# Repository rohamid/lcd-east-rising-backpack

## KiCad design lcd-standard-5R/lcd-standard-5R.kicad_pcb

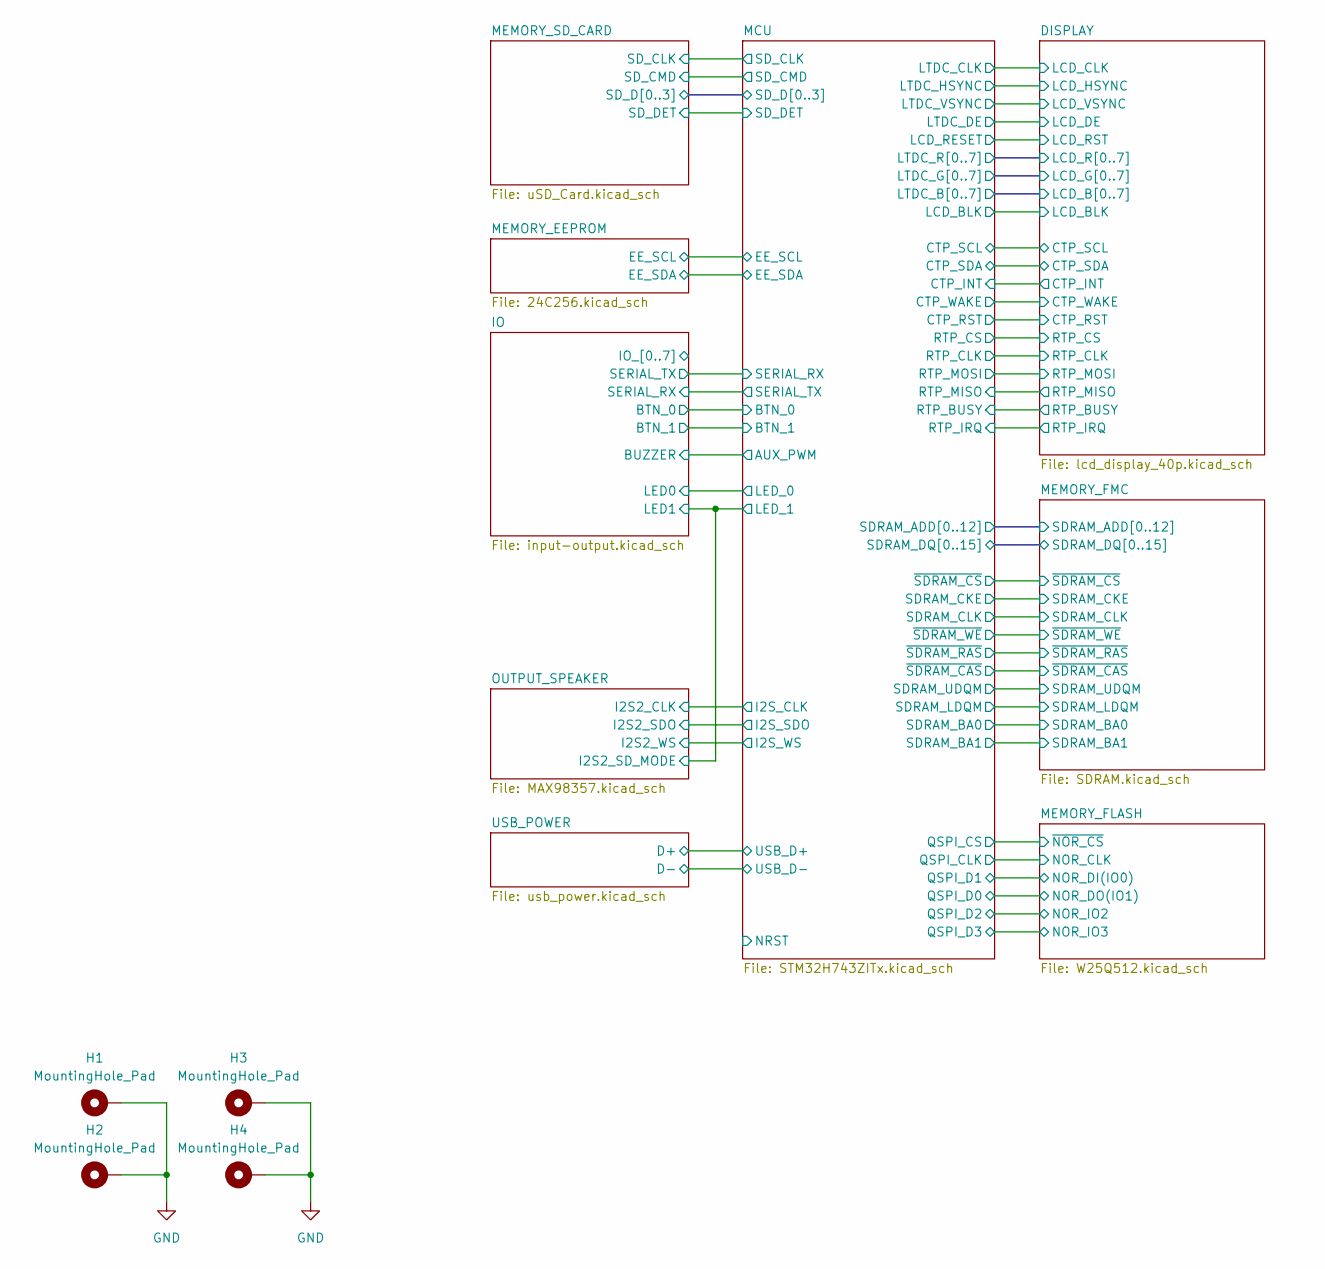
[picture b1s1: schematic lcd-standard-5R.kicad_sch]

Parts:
H1, H2, H3, H4: MountingHole_Pad; MountingHole_3.2mm_M3_Pad_Via

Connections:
GND: H1.1, H2.1, H3.1, H4.1; also elsewhere on the board

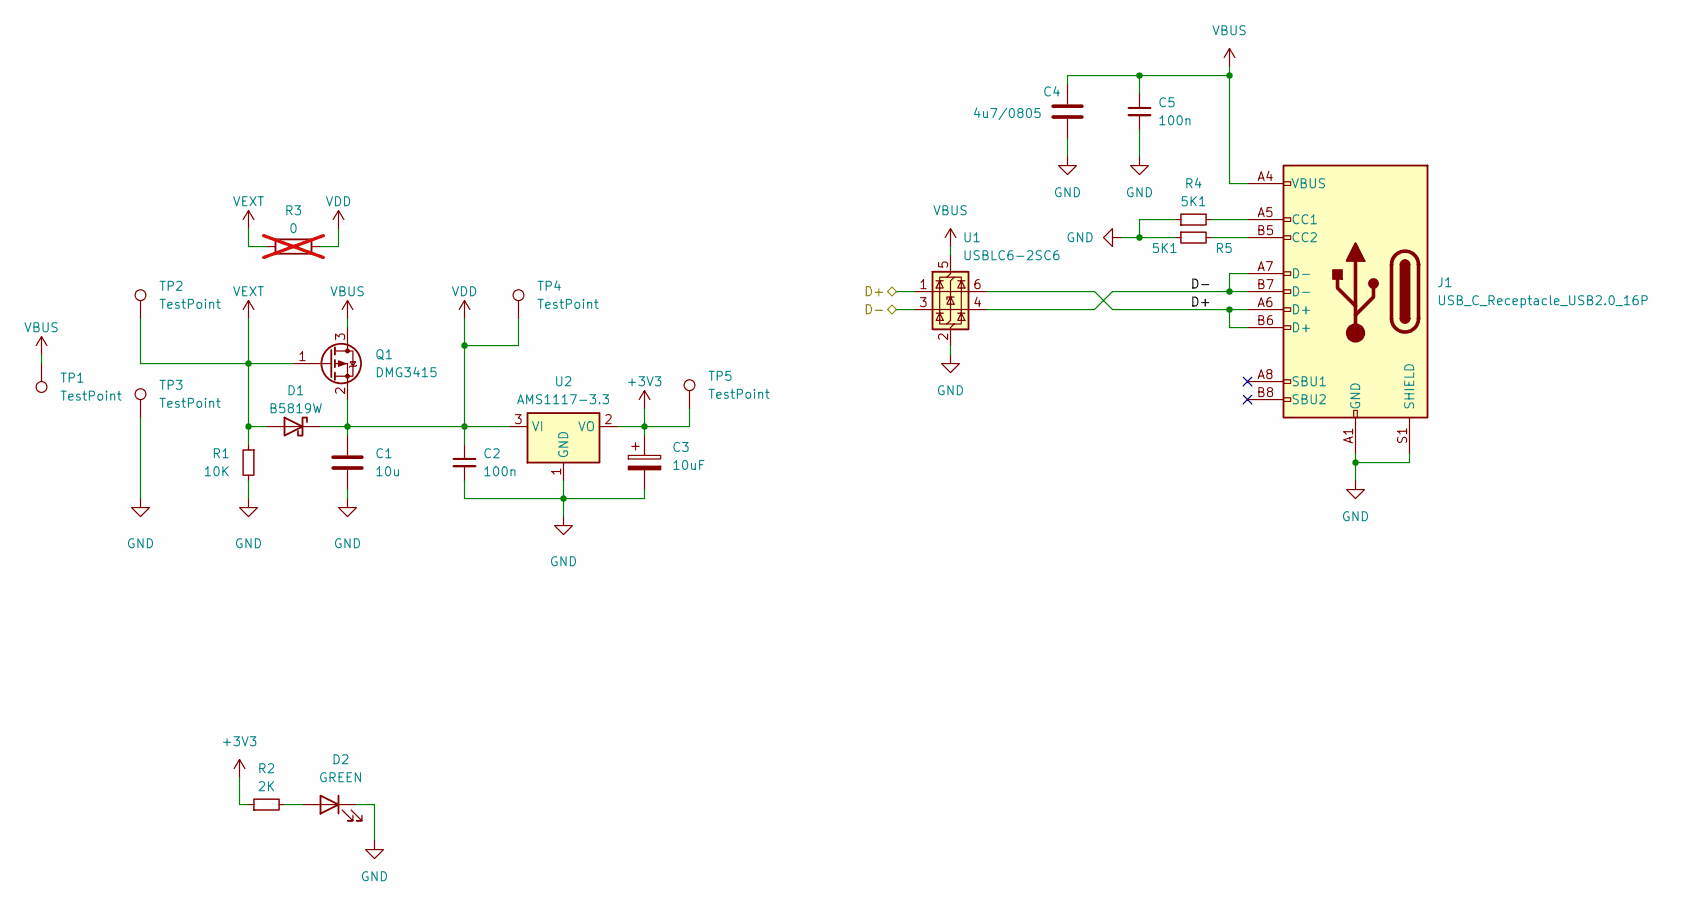
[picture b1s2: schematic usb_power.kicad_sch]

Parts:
C1: 10u; C_0805_2012Metric; JLCPCB Part # C15850
C2, C5: 100n; C_0402_1005Metric; JLCPCB Part # C307331
C3: 10uF; CP_EIA-3216-18_Kemet-A; JLCPCB Part # C7171
C4: 4u7/0805; C_0805_2012Metric; JLCPCB Part # C1779
D1: B5819W; D_SOD-123; JLCPCB Part # C7420330
D2: GREEN; LED_0805_2012Metric; JLCPCB Part # C2297
J1: USB_C_Receptacle_USB2.0_16P; USB_C_Receptacle_G-Switch_GT-USB-7010ASV; JLCPCB Part # C963412
Q1: DMG3415; SOT-23; JLCPCB Part # C7202986
R1: 10K; R_0402_1005Metric; JLCPCB Part # C25744
R2: 2K; R_0402_1005Metric; JLCPCB Part # C4109
R3: 0; R_1206_3216Metric; not fitted
R4, R5: 5K1; R_0402_1005Metric; JLCPCB Part # C25905
TP1, TP2, TP3, TP4, TP5: TestPoint; TestPoint_Pad_D1.0mm
U1: USBLC6-2SC6; SOT-23-6; JLCPCB Part # C2827654
U2: AMS1117-3.3; SOT-223-3_TabPin2; JLCPCB Part # C6186

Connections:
+3V3: C3.1, R2.1, TP5.1, U2.2 (VO); also elsewhere on the board
/USB_POWER/D+: J1.A6 (D+), J1.B6 (D+), U1.1 (I/O1), U1.6 (I/O1); also elsewhere on the board
/USB_POWER/D-: J1.A7 (D-), J1.B7 (D-), U1.3 (I/O2), U1.4 (I/O2); also elsewhere on the board
GND: C1.2, C2.2, C3.2, C4.2, C5.2, D2.1 (K), J1.A1 (GND), J1.A12 (GND), J1.B1 (GND), J1.B12 (GND), J1.S1 (SHIELD), R1.2, R4.1, R5.1, TP3.1, U1.2 (GND), U2.1 (GND); also elsewhere on the board
unnamed: D2.2 (A), R2.2
unnamed: J1.A5 (CC1), R4.2
unnamed: J1.B5 (CC2), R5.2
VBUS: C4.1, C5.1, J1.A4 (VBUS), J1.A9 (VBUS), J1.B4 (VBUS), J1.B9 (VBUS), Q1.3 (D), TP1.1, U1.5 (VBUS)
VDD: C1.1, C2.1, D1.1 (K), Q1.2 (S), R3.2, TP4.1, U2.3 (VI); also elsewhere on the board
VEXT: D1.2 (A), Q1.1 (G), R1.1, R3.1, TP2.1; also elsewhere on the board

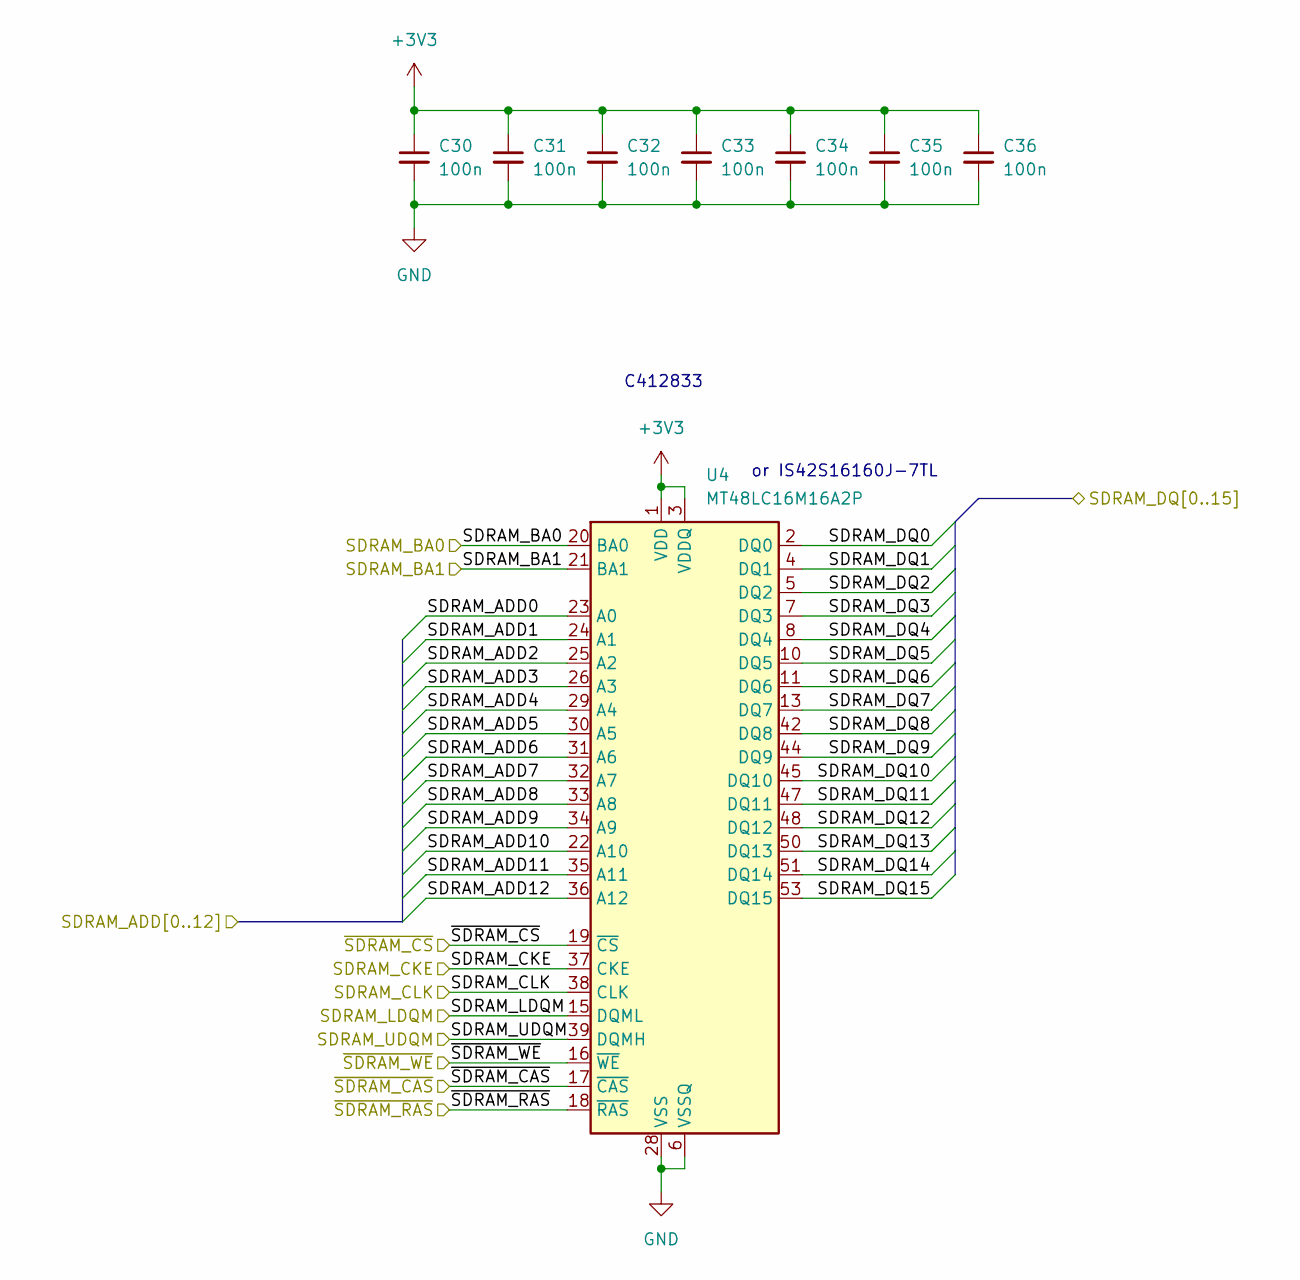
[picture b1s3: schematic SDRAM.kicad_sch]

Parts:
C30, C31, C32, C33, C34, C35, C36: 100n; C_0402_1005Metric; JLCPCB Part # C307331
U4: MT48LC16M16A2P; TSOP-II-54_22.2x10.16mm_P0.8mm; JLCPCB Part # C412833

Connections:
+3V3: C30.1, C31.1, C32.1, C33.1, C34.1, C35.1, C36.1, U4.1 (VDD), U4.3 (VDDQ), U4.9 (VDDQ), U4.14 (VDD), U4.27 (VDD), U4.43 (VDDQ), U4.49 (VDDQ); also elsewhere on the board
/MCU/SDRAM_ADD0: U4.23 (A0); also elsewhere on the board
/MCU/SDRAM_ADD1: U4.24 (A1); also elsewhere on the board
/MCU/SDRAM_ADD2: U4.25 (A2); also elsewhere on the board
/MCU/SDRAM_ADD3: U4.26 (A3); also elsewhere on the board
/MCU/SDRAM_ADD4: U4.29 (A4); also elsewhere on the board
/MCU/SDRAM_ADD5: U4.30 (A5); also elsewhere on the board
/MCU/SDRAM_ADD6: U4.31 (A6); also elsewhere on the board
/MCU/SDRAM_ADD7: U4.32 (A7); also elsewhere on the board
/MCU/SDRAM_ADD8: U4.33 (A8); also elsewhere on the board
/MCU/SDRAM_ADD9: U4.34 (A9); also elsewhere on the board
/MCU/SDRAM_ADD10: U4.22 (A10); also elsewhere on the board
/MCU/SDRAM_ADD11: U4.35 (A11); also elsewhere on the board
/MCU/SDRAM_ADD12: U4.36 (A12); also elsewhere on the board
/MCU/SDRAM_DQ0: U4.2 (DQ0); also elsewhere on the board
/MCU/SDRAM_DQ1: U4.4 (DQ1); also elsewhere on the board
/MCU/SDRAM_DQ2: U4.5 (DQ2); also elsewhere on the board
/MCU/SDRAM_DQ3: U4.7 (DQ3); also elsewhere on the board
/MCU/SDRAM_DQ4: U4.8 (DQ4); also elsewhere on the board
/MCU/SDRAM_DQ5: U4.10 (DQ5); also elsewhere on the board
/MCU/SDRAM_DQ6: U4.11 (DQ6); also elsewhere on the board
/MCU/SDRAM_DQ7: U4.13 (DQ7); also elsewhere on the board
/MCU/SDRAM_DQ8: U4.42 (DQ8); also elsewhere on the board
/MCU/SDRAM_DQ9: U4.44 (DQ9); also elsewhere on the board
/MCU/SDRAM_DQ10: U4.45 (DQ10); also elsewhere on the board
/MCU/SDRAM_DQ11: U4.47 (DQ11); also elsewhere on the board
/MCU/SDRAM_DQ12: U4.48 (DQ12); also elsewhere on the board
/MCU/SDRAM_DQ13: U4.50 (DQ13); also elsewhere on the board
/MCU/SDRAM_DQ14: U4.51 (DQ14); also elsewhere on the board
/MCU/SDRAM_DQ15: U4.53 (DQ15); also elsewhere on the board
/MEMORY_FMC/SDRAM_BA0: U4.20 (BA0); also elsewhere on the board
/MEMORY_FMC/SDRAM_BA1: U4.21 (BA1); also elsewhere on the board
/MEMORY_FMC/SDRAM_CKE: U4.37 (CKE); also elsewhere on the board
/MEMORY_FMC/SDRAM_CLK: U4.38 (CLK); also elsewhere on the board
/MEMORY_FMC/SDRAM_LDQM: U4.15 (DQML); also elsewhere on the board
/MEMORY_FMC/SDRAM_UDQM: U4.39 (DQMH); also elsewhere on the board
/MEMORY_FMC/~SDRAM_CAS: U4.17 (~CAS); also elsewhere on the board
/MEMORY_FMC/~SDRAM_CS: U4.19 (~CS); also elsewhere on the board
/MEMORY_FMC/~SDRAM_RAS: U4.18 (~RAS); also elsewhere on the board
/MEMORY_FMC/~SDRAM_WE: U4.16 (~WE); also elsewhere on the board
GND: C30.2, C31.2, C32.2, C33.2, C34.2, C35.2, C36.2, U4.6 (VSSQ), U4.12 (VSSQ), U4.28 (VSS), U4.41 (VSS), U4.46 (VSSQ), U4.52 (VSSQ), U4.54 (VSS); also elsewhere on the board

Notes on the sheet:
C412833
or IS42S16160J-7TL

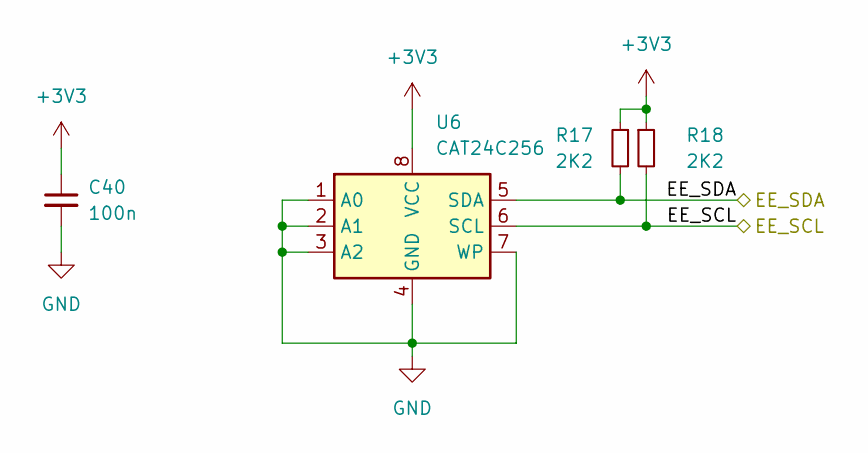
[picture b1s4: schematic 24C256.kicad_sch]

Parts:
C40: 100n; C_0402_1005Metric; JLCPCB Part # C307331
R17, R18: 2K2; R_0402_1005Metric; JLCPCB Part # C25879
U6: CAT24C256; SOIC-8_3.9x4.9mm_P1.27mm; JLCPCB Part # C6482

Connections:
+3V3: C40.1, R17.1, R18.1, U6.8 (VCC); also elsewhere on the board
/MEMORY_EEPROM/EE_SCL: R18.2, U6.6 (SCL); also elsewhere on the board
/MEMORY_EEPROM/EE_SDA: R17.2, U6.5 (SDA); also elsewhere on the board
GND: C40.2, U6.1 (A0), U6.2 (A1), U6.3 (A2), U6.4 (GND), U6.7 (WP); also elsewhere on the board

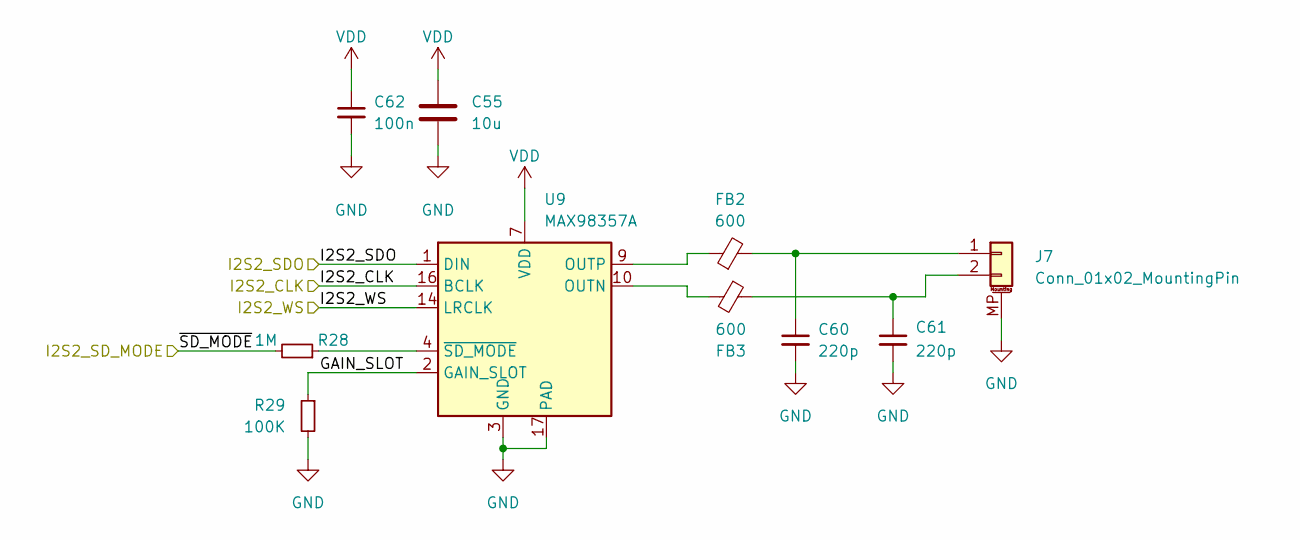
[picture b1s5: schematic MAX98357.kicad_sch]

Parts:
C55: 10u; C_0805_2012Metric; JLCPCB Part # C15850
C60, C61: 220p; C_0805_2012Metric; JLCPCB Part # C107145
C62: 100n; C_0402_1005Metric; JLCPCB Part # C307331
FB2, FB3: 600; L_0805_2012Metric; JLCPCB Part # C1017
J7: Conn_01x02_MountingPin; Hirose_DF13C_CL535-0402-2-51_1x02-1MP_P1.25mm_Vertical; JLCPCB Part # C7419891
R28: 1M; R_0402_1005Metric; JLCPCB Part # C26083
R29: 100K; R_0402_1005Metric; JLCPCB Part # C25741
U9: MAX98357A; TQFN-16-1EP_3x3mm_P0.5mm_EP1.23x1.23mm; JLCPCB Part # C910544

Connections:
/OUTPUT_SPEAKER/GAIN_SLOT: R29.1, U9.2 (GAIN_SLOT)
/OUTPUT_SPEAKER/I2S2_CLK: U9.16 (BCLK); also elsewhere on the board
/OUTPUT_SPEAKER/I2S2_SDO: U9.1 (DIN); also elsewhere on the board
/OUTPUT_SPEAKER/I2S2_WS: U9.14 (LRCLK); also elsewhere on the board
/OUTPUT_SPEAKER/~SD_MODE: R28.2; also elsewhere on the board
GND: C55.2, C60.2, C61.2, C62.2, J7.MP (MountPin), R29.2, U9.3 (GND), U9.11 (GND), U9.15 (GND), U9.17 (PAD); also elsewhere on the board
unnamed: C60.1, FB2.2, J7.1
unnamed: C61.1, FB3.1, J7.2
unnamed: FB3.2, U9.10 (OUTN)
unnamed: FB2.1, U9.9 (OUTP)
unnamed: R28.1, U9.4 (~SD_MODE)
VDD: C55.1, C62.1, U9.7 (VDD), U9.8 (VDD); also elsewhere on the board

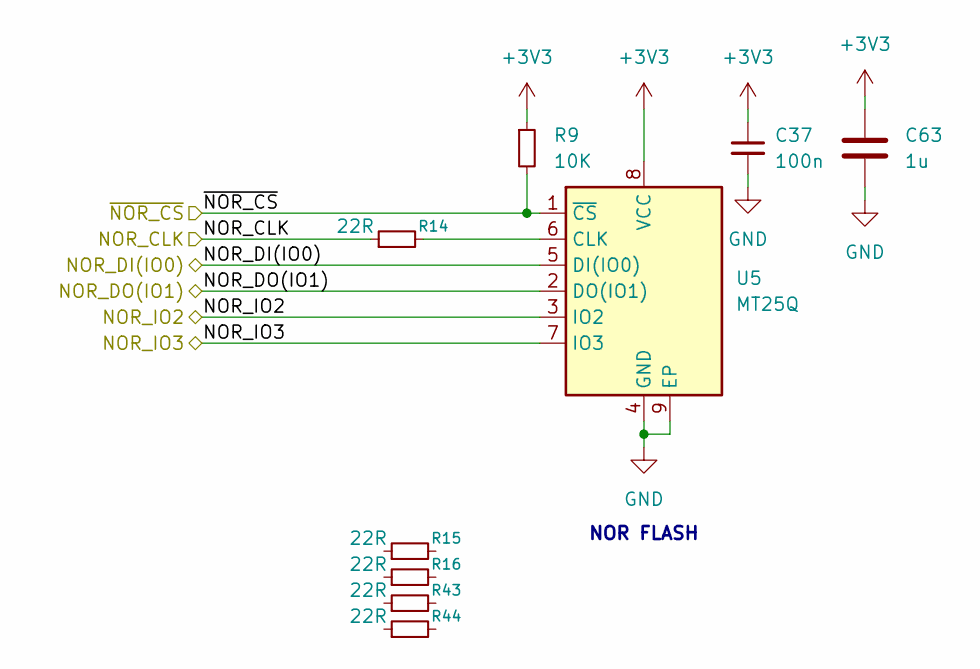
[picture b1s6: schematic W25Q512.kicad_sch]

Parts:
C37: 100n; C_0402_1005Metric; JLCPCB Part # C307331
C63: 1u; C_0603_1608Metric; JLCPCB Part # C15849
R9: 10K; R_0402_1005Metric; JLCPCB Part # C25744
R14, R15, R16, R43, R44: 22R; R_0201_0603Metric
U5: MT25Q; SON127P800X600X80-9N; JLCPCB Part # C2061007

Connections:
+3V3: C37.1, C63.1, R9.1, U5.8 (VCC); also elsewhere on the board
/MEMORY_FLASH/NOR_CLK: R14.1; also elsewhere on the board
/MEMORY_FLASH/NOR_DI(IO0): U5.5 (DI(IO0)); also elsewhere on the board
/MEMORY_FLASH/NOR_DO(IO1): U5.2 (DO(IO1)); also elsewhere on the board
/MEMORY_FLASH/NOR_IO2: U5.3 (IO2); also elsewhere on the board
/MEMORY_FLASH/NOR_IO3: U5.7 (IO3); also elsewhere on the board
/MEMORY_FLASH/~NOR_CS: R9.2, U5.1 (~CS); also elsewhere on the board
GND: C37.2, C63.2, U5.4 (GND), U5.9 (EP); also elsewhere on the board
unnamed: R14.2, U5.6 (CLK)

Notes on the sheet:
NOR FLASH

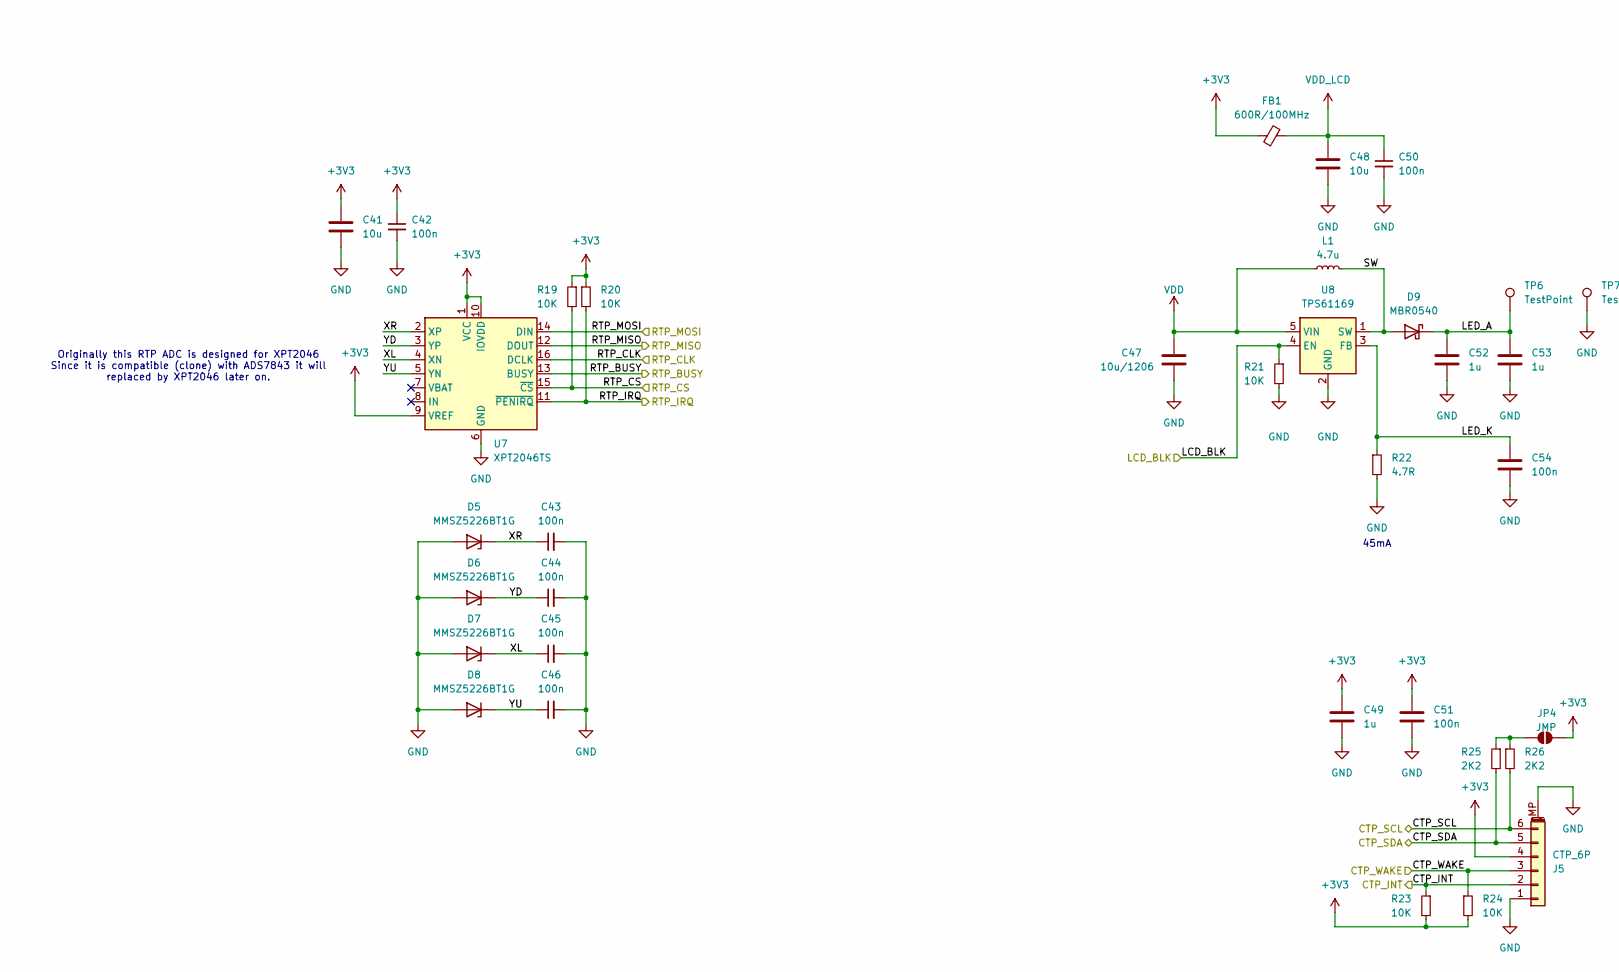
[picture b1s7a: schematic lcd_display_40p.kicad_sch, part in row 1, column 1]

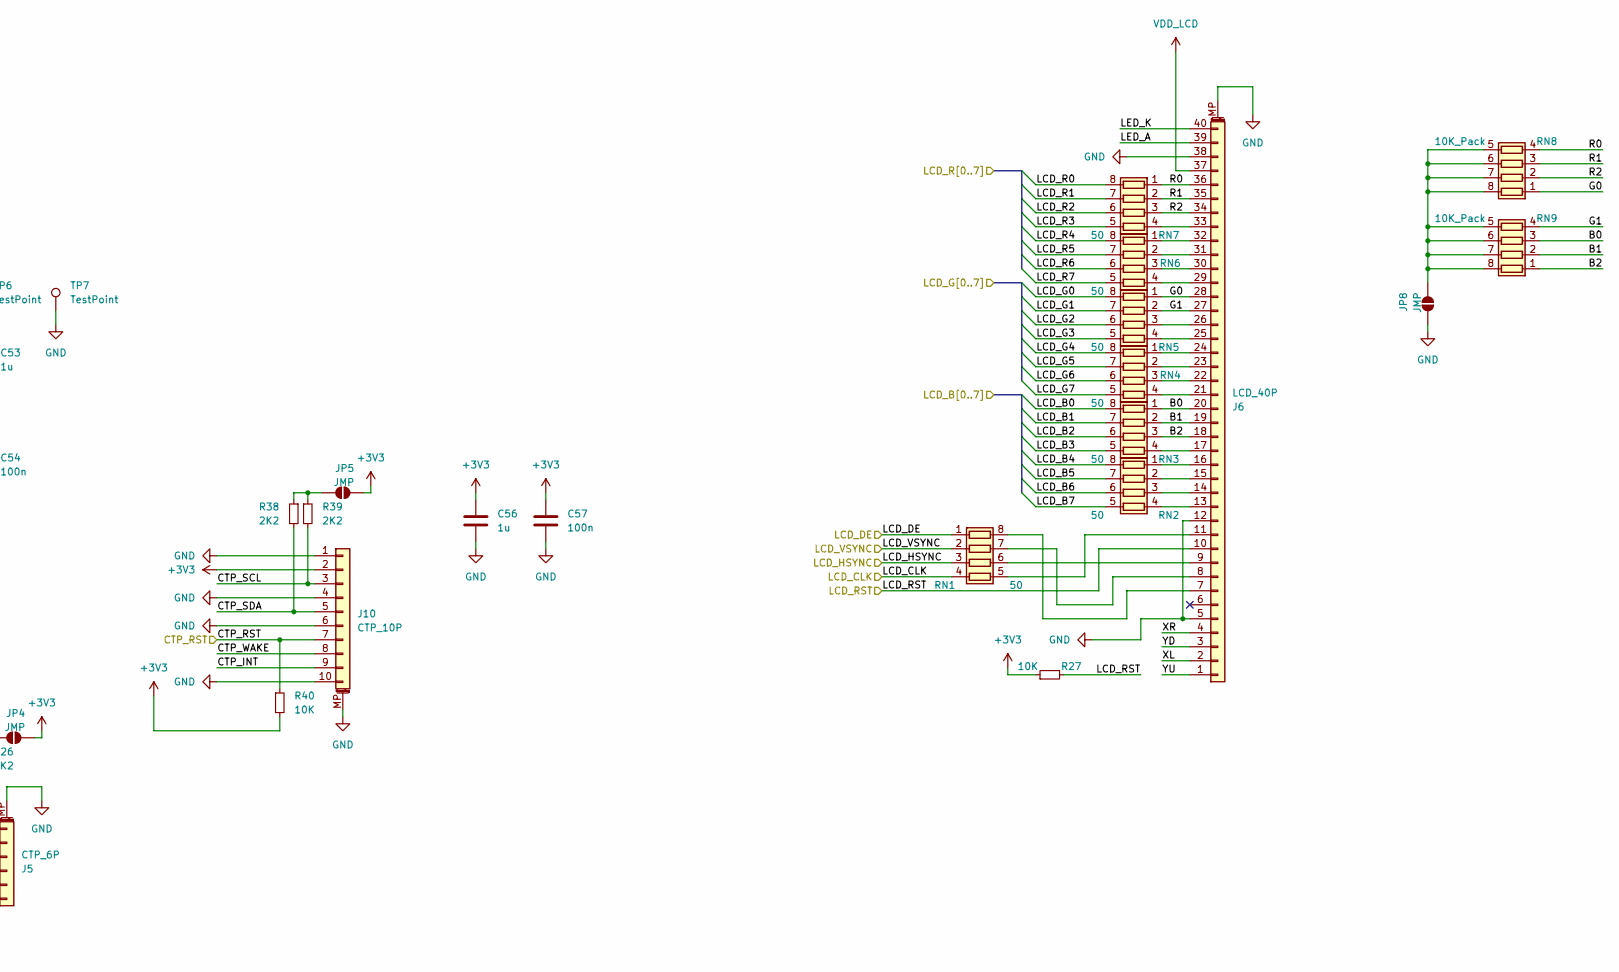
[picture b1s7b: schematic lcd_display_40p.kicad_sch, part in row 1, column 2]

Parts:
C41, C48: 10u; C_0805_2012Metric; JLCPCB Part # C15850
C42, C43, C44, C45, C46, C50, C51, C54, C57: 100n; C_0402_1005Metric; JLCPCB Part # C307331
C47: 10u/1206; C_1206_3216Metric; JLCPCB Part # C13585
C49, C52, C53, C56: 1u; C_0603_1608Metric; JLCPCB Part # C15849
D5, D6, D7, D8: MMSZ5226BT1G; D_SOD-123; JLCPCB Part # C235771
D9: MBR0540; D_SOD-123; JLCPCB Part # C7420330
FB1: 600R/100MHz; C_0805_2012Metric; JLCPCB Part # C1017
J5: CTP_6P; Conn_FPC_6P_0.5mm_XUNPU_FPC-05FB-6PH20; JLCPCB Part # C2856827
J6: LCD_40P; Omron_XF2M-4015-1A_1x40-1MP_P0.5mm_Horizontal; JLCPCB Part # C225713
J10: CTP_10P; Conn_FPC_10P_0.5mm_OMRON_XF2M-1015-1A; JLCPCB Part # C271735
JP4, JP5, JP8: JMP; SolderJumper-2_P1.3mm_Open_RoundedPad1.0x1.5mm
L1: 4.7u; L_Abracon_ASPI-4030S; JLCPCB Part # C57269
R19, R20, R21, R23, R24, R27, R40: 10K; R_0402_1005Metric; JLCPCB Part # C25744
R22: 4.7R; R_0603_1608Metric; JLCPCB Part # C23164
R25, R26, R38, R39: 2K2; R_0402_1005Metric; JLCPCB Part # C25879
RN1, RN2, RN3, RN4, RN5, RN6, RN7: 50; R_Array_Convex_4x0402; JLCPCB Part # C48442
RN8, RN9: 10K_Pack; R_Array_Convex_4x0402; JLCPCB Part # C25725
TP6, TP7: TestPoint; TestPoint_Pad_D1.0mm
U7: XPT2046TS; TSSOP-16_4.4x5mm_P0.65mm; JLCPCB Part # C364888
U8: TPS61169; SOT-353_SC-70-5; JLCPCB Part # C71045

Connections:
+3V3: C41.1, C42.1, C49.1, C51.1, C56.1, C57.1, FB1.1, J5.4, J10.2, JP4.2 (B), JP5.2 (B), R19.1, R20.1, R23.2, R24.2, R27.1, R40.2, U7.1 (VCC), U7.9 (VREF), U7.10 (IOVDD); also elsewhere on the board
/DISPLAY/B0: J6.20, RN3.1 (R1.1), RN9.3 (R3.1)
/DISPLAY/B1: J6.19, RN3.2 (R2.1), RN9.2 (R2.1)
/DISPLAY/B2: J6.18, RN3.3 (R3.1), RN9.1 (R1.1)
/DISPLAY/CTP_INT: J5.2, J10.9, R23.1; also elsewhere on the board
/DISPLAY/CTP_RST: J10.7, R40.1; also elsewhere on the board
/DISPLAY/CTP_SCL: J5.6, J10.3, R26.2, R39.2; also elsewhere on the board
/DISPLAY/CTP_SDA: J5.5, J10.5, R25.2, R38.2; also elsewhere on the board
/DISPLAY/CTP_WAKE: J5.3, J10.8, R24.1; also elsewhere on the board
/DISPLAY/G0: J6.28, RN5.1 (R1.1), RN8.1 (R1.1)
/DISPLAY/G1: J6.27, RN5.2 (R2.1), RN9.4 (R4.1)
/DISPLAY/LCD_B0: RN3.8 (R1.2); also elsewhere on the board
/DISPLAY/LCD_B1: RN3.7 (R2.2); also elsewhere on the board
/DISPLAY/LCD_B2: RN3.6 (R3.2); also elsewhere on the board
/DISPLAY/LCD_B3: RN3.5 (R4.2); also elsewhere on the board
/DISPLAY/LCD_B4: RN2.8 (R1.2); also elsewhere on the board
/DISPLAY/LCD_B5: RN2.7 (R2.2); also elsewhere on the board
/DISPLAY/LCD_B6: RN2.6 (R3.2); also elsewhere on the board
/DISPLAY/LCD_B7: RN2.5 (R4.2); also elsewhere on the board
/DISPLAY/LCD_BLK: R21.1, U8.4 (EN); also elsewhere on the board
/DISPLAY/LCD_CLK: RN1.4 (R4.1); also elsewhere on the board
/DISPLAY/LCD_DE: RN1.1 (R1.1); also elsewhere on the board
/DISPLAY/LCD_G0: RN5.8 (R1.2); also elsewhere on the board
/DISPLAY/LCD_G1: RN5.7 (R2.2); also elsewhere on the board
/DISPLAY/LCD_G2: RN5.6 (R3.2); also elsewhere on the board
/DISPLAY/LCD_G3: RN5.5 (R4.2); also elsewhere on the board
/DISPLAY/LCD_G4: RN4.8 (R1.2); also elsewhere on the board
/DISPLAY/LCD_G5: RN4.7 (R2.2); also elsewhere on the board
/DISPLAY/LCD_G6: RN4.6 (R3.2); also elsewhere on the board
/DISPLAY/LCD_G7: RN4.5 (R4.2); also elsewhere on the board
/DISPLAY/LCD_HSYNC: RN1.3 (R3.1); also elsewhere on the board
/DISPLAY/LCD_R0: RN7.8 (R1.2); also elsewhere on the board
/DISPLAY/LCD_R1: RN7.7 (R2.2); also elsewhere on the board
/DISPLAY/LCD_R2: RN7.6 (R3.2); also elsewhere on the board
/DISPLAY/LCD_R3: RN7.5 (R4.2); also elsewhere on the board
/DISPLAY/LCD_R4: RN6.8 (R1.2); also elsewhere on the board
/DISPLAY/LCD_R5: RN6.7 (R2.2); also elsewhere on the board
/DISPLAY/LCD_R6: RN6.6 (R3.2); also elsewhere on the board
/DISPLAY/LCD_R7: RN6.5 (R4.2); also elsewhere on the board
/DISPLAY/LCD_RST: J6.10, R27.2
/DISPLAY/LCD_VSYNC: RN1.2 (R2.1); also elsewhere on the board
/DISPLAY/LED_A: C52.1, C53.1, D9.1 (K), J6.39, TP6.1
/DISPLAY/LED_K: C54.1, J6.40, R22.1, U8.3 (FB)
/DISPLAY/R0: J6.36, RN7.1 (R1.1), RN8.4 (R4.1)
/DISPLAY/R1: J6.35, RN7.2 (R2.1), RN8.3 (R3.1)
/DISPLAY/R2: J6.34, RN7.3 (R3.1), RN8.2 (R2.1)
/DISPLAY/RTP_BUSY: U7.13 (BUSY); also elsewhere on the board
/DISPLAY/RTP_CLK: U7.16 (DCLK); also elsewhere on the board
/DISPLAY/RTP_CS: R19.2, U7.15 (~CS); also elsewhere on the board
/DISPLAY/RTP_IRQ: R20.2, U7.11 (~PENIRQ); also elsewhere on the board
/DISPLAY/RTP_MISO: U7.12 (DOUT); also elsewhere on the board
/DISPLAY/RTP_MOSI: U7.14 (DIN); also elsewhere on the board
/DISPLAY/SW: D9.2 (A), L1.2, U8.1 (SW)
/DISPLAY/XL: C45.1, D7.1 (K), J6.2, U7.4 (XN)
/DISPLAY/XR: C43.1, D5.1 (K), J6.4, U7.2 (XP)
/DISPLAY/YD: C44.1, D6.1 (K), J6.3, U7.3 (YP)
/DISPLAY/YU: C46.1, D8.1 (K), J6.1, U7.5 (YN)
GND: C41.2, C42.2, C43.2, C44.2, C45.2, C46.2, C47.2, C48.2, C49.2, C50.2, C51.2, C52.2, C53.2, C54.2, C56.2, C57.2, D5.2 (A), D6.2 (A), D7.2 (A), D8.2 (A), J5.1, J5.MP (MountPin), J6.5, J6.12, J6.38, J6.MP (MountPin), J10.1, J10.4, J10.6, J10.10, J10.MP (MountPin), JP8.1 (A), R21.2, R22.2, TP7.1, U7.6 (GND), U8.2 (GND); also elsewhere on the board
unnamed: J6.7, RN1.8 (R1.2)
unnamed: J6.8, RN1.7 (R2.2)
unnamed: J6.9, RN1.6 (R3.2)
unnamed: J6.11, RN1.5 (R4.2)
unnamed: J6.13, RN2.4 (R4.1)
unnamed: J6.14, RN2.3 (R3.1)
unnamed: J6.15, RN2.2 (R2.1)
unnamed: J6.16, RN2.1 (R1.1)
unnamed: J6.17, RN3.4 (R4.1)
unnamed: J6.21, RN4.4 (R4.1)
unnamed: J6.22, RN4.3 (R3.1)
unnamed: J6.23, RN4.2 (R2.1)
unnamed: J6.24, RN4.1 (R1.1)
unnamed: J6.25, RN5.4 (R4.1)
unnamed: J6.26, RN5.3 (R3.1)
unnamed: J6.29, RN6.4 (R4.1)
unnamed: J6.30, RN6.3 (R3.1)
unnamed: J6.31, RN6.2 (R2.1)
unnamed: J6.32, RN6.1 (R1.1)
unnamed: J6.33, RN7.4 (R4.1)
unnamed: JP4.1 (A), R25.1, R26.1
unnamed: JP5.1 (A), R38.1, R39.1
unnamed: JP8.2 (B), RN8.5 (R4.2), RN8.6 (R3.2), RN8.7 (R2.2), RN8.8 (R1.2), RN9.5 (R4.2), RN9.6 (R3.2), RN9.7 (R2.2), RN9.8 (R1.2)
VDD: C47.1, L1.1, U8.5 (VIN); also elsewhere on the board
VDD_LCD: C48.1, C50.1, FB1.2, J6.37

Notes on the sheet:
Originally this RTP ADC is designed for XPT2046 Since it is compatible (clone) with ADS7843 it will replaced by XPT2046 later on.
45mA

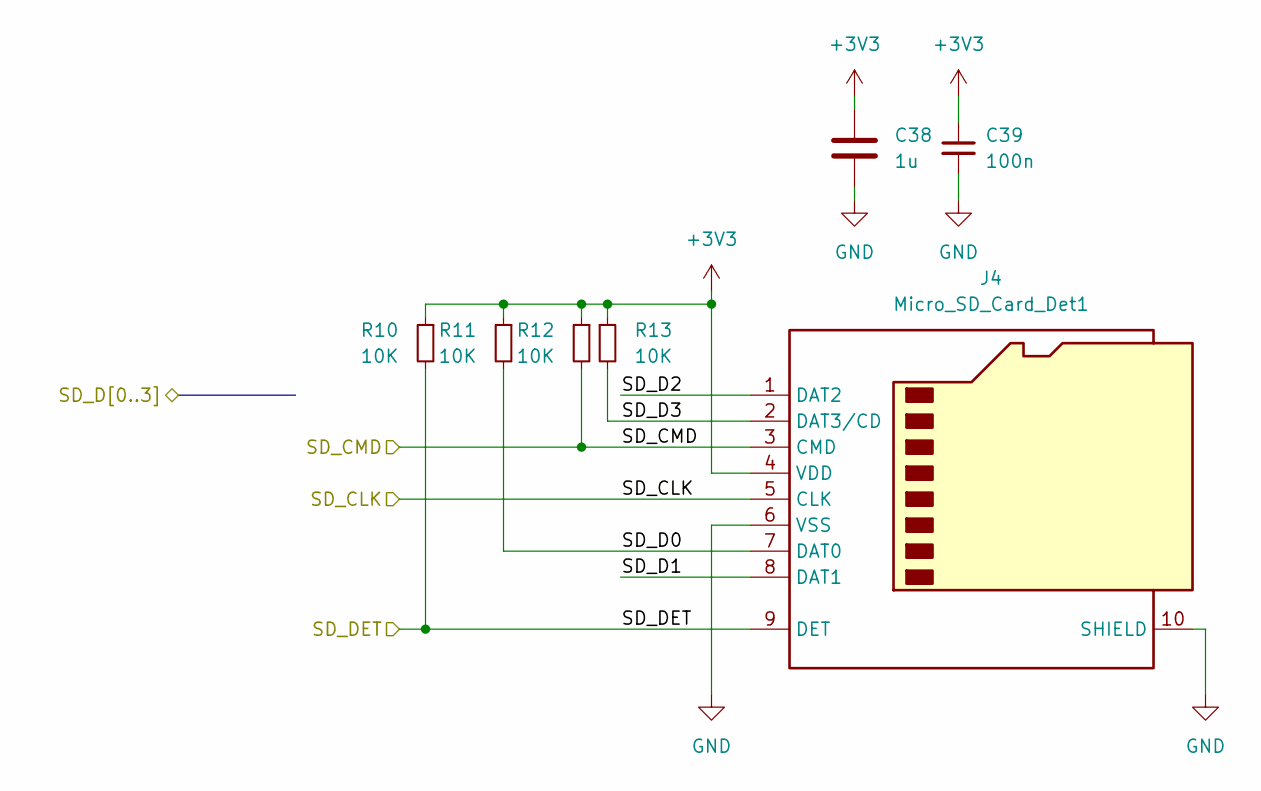
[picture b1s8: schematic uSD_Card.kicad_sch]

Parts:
C38: 1u; C_0603_1608Metric; JLCPCB Part # C15849
C39: 100n; C_0402_1005Metric; JLCPCB Part # C307331
J4: Micro_SD_Card_Det1; SD-TF-115; JLCPCB Part # C266621
R10, R11, R12, R13: 10K; R_0402_1005Metric; JLCPCB Part # C25744

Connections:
+3V3: C38.1, C39.1, J4.4 (VDD), R10.1, R11.1, R12.1, R13.1; also elsewhere on the board
/MCU/SD_D0: J4.7 (DAT0), R11.2; also elsewhere on the board
/MCU/SD_D1: J4.8 (DAT1); also elsewhere on the board
/MCU/SD_D2: J4.1 (DAT2); also elsewhere on the board
/MCU/SD_D3: J4.2 (DAT3/CD), R13.2; also elsewhere on the board
/MEMORY_SD_CARD/SD_CLK: J4.5 (CLK); also elsewhere on the board
/MEMORY_SD_CARD/SD_CMD: J4.3 (CMD), R12.2; also elsewhere on the board
/MEMORY_SD_CARD/SD_DET: J4.9 (DET), R10.2; also elsewhere on the board
GND: C38.2, C39.2, J4.6 (VSS), J4.10 (SHIELD); also elsewhere on the board
